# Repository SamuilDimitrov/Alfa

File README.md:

# Alfa

*Alfa представлява модел на ракета която моще да извършва стабилни полети като за стабилизация изполва насочване на вектора на изходните газове на двигателя*

## Как да си сваля и използвам проекта?

За сега не е невъзможно.

## Използвани технологии

* Arduino(https://www.arduino.cc/) - микро контролер
* MPU6050(https://invensense.tdk.com/products/motion-tracking/6-axis/mpu-6050/) - комбиниран акселерометър и жироскоп определящи посоката и ориентацията на ракетата
* BME280(https://www.bosch-sensortec.com/products/environmental-sensors/humidity-sensors-bme280/) - сензор за температура и атмосферно налягане

## Информация за авторите на проекта

* **Самуил Димитров** - *програмист, дизаинер, хардуерист*

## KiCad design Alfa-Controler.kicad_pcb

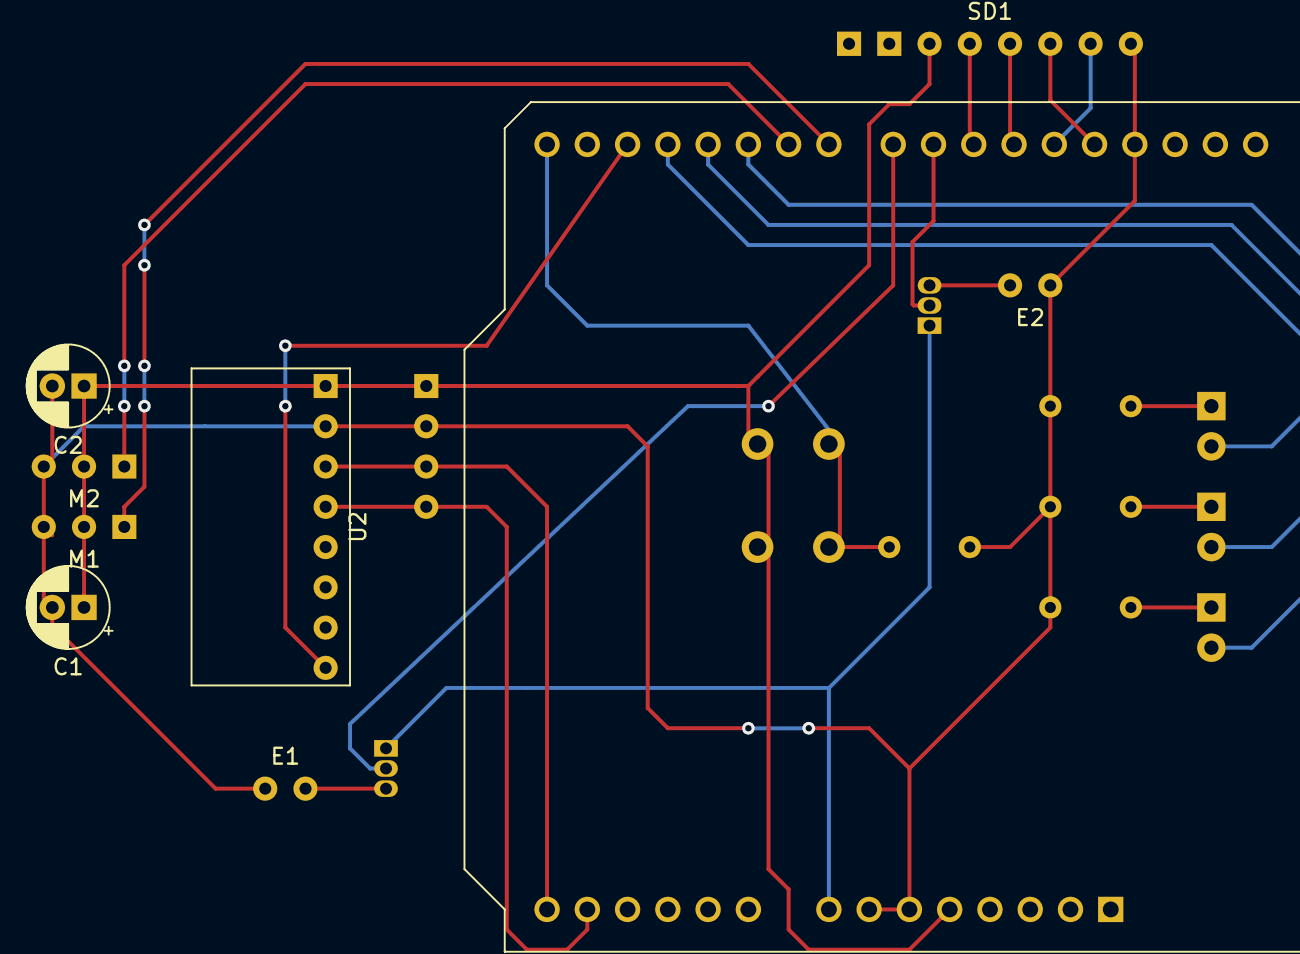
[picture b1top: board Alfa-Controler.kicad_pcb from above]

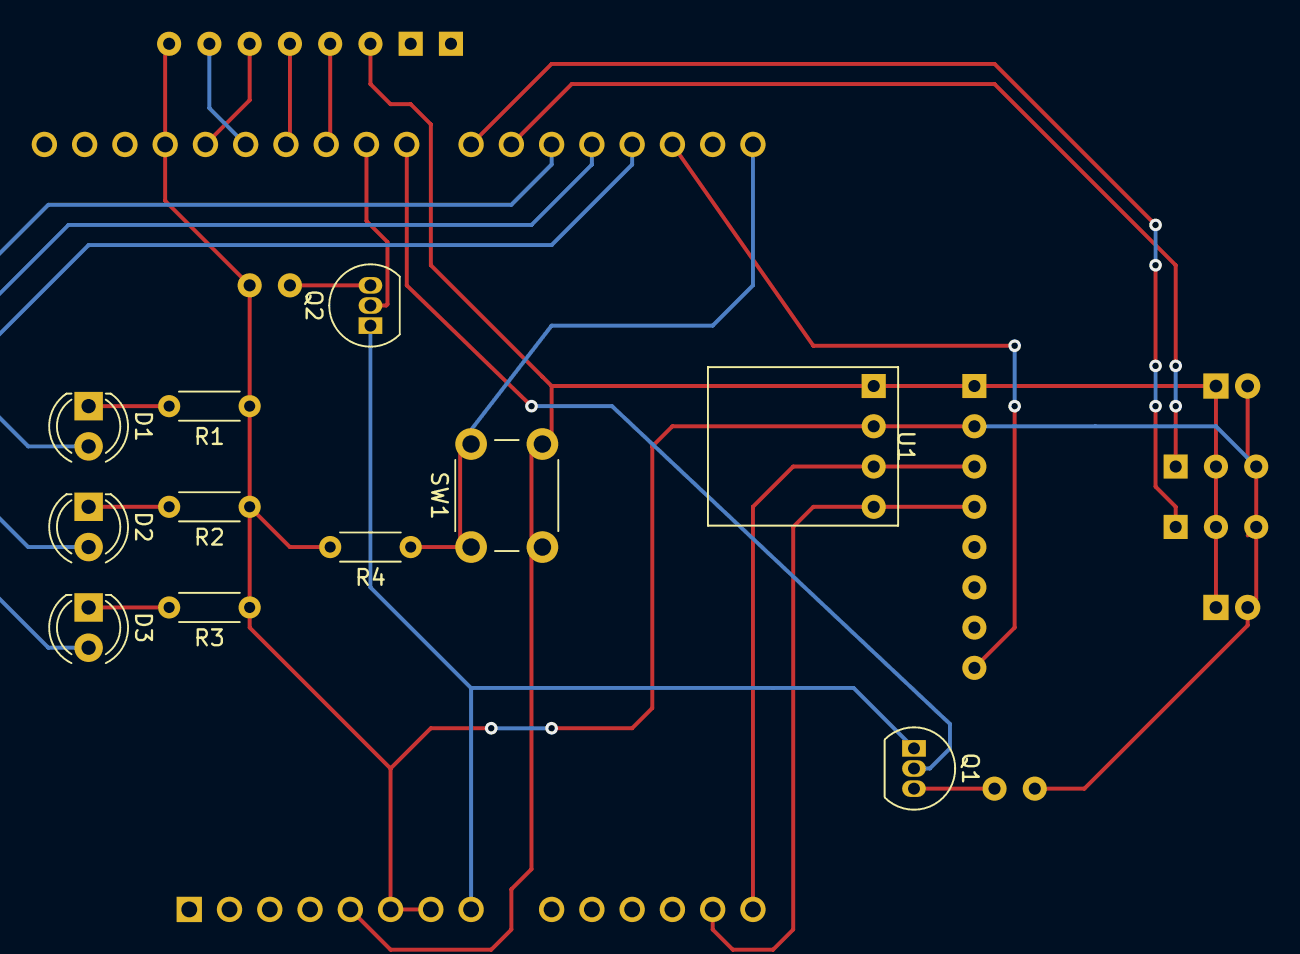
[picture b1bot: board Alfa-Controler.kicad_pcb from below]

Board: 2 copper layers, 20 parts (11 on the bottom side), 23 nets.

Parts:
A1: Arduino_UNO_R3
C1, C2: 100uF; CP_Radial_D5.0mm_P2.00mm
D1: BLUE_LED; LED_D4.0mm
D2: GREEN_LED; LED_D4.0mm
D3: RED_LED; LED_D4.0mm
E1: Ignition_SPARK_GAP; Spark_cable
E2: Piro1_SPARK_GAP; Spark_cable
M1: X-axis Servo; Servo_Pins
M2: Y-axis Servo; Servo_Pins
Q1, Q2: 2N3904; TO-92_Inline
R1, R2, R3: 220; R_Axial_DIN0204_L3.6mm_D1.6mm_P5.08mm_Horizontal
R4: 10k; R_Axial_DIN0204_L3.6mm_D1.6mm_P5.08mm_Horizontal
SD1: SD_CARD
SW1: SW_Push; SW_PUSH_6mm_H4.3mm
U1: BME280_BB; BMP280
U2: MPU-6050BB; MPU6050

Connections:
+5V: A1.5, C1.1, C2.1, M1.2, M2.2, SD1.3, SW1.2, U1.1, U2.1
+9V: A1.8, Q1.1, Q2.1
/D6: A1.21, M2.1
/D7: A1.22, M1.1
/D8: A1.23, Q1.2
/D9: A1.24, Q2.2
/INT: A1.17, U2.8
/SCL_BMP: A1.14, U1.3, U2.3
/SDA_BMP: A1.13, U1.4, U2.4
GND: A1.6, A1.7, A1.29, C1.2, C2.2, E1.1, E2.1, M1.3, M2.3, R1.1, R2.1, R3.1, R4.2, SD1.8, U1.2, U2.2
unnamed: A1.15, R4.1, SW1.1
unnamed: A1.18, D1.2
unnamed: A1.19, D2.2
unnamed: A1.20, D3.2
unnamed: A1.25, SD1.4
unnamed: A1.26, SD1.5
unnamed: A1.27, SD1.7
unnamed: A1.28, SD1.6
unnamed: D1.1, R1.2
unnamed: D2.1, R2.2
unnamed: D3.1, R3.2
unnamed: E1.2, Q1.3
unnamed: E2.2, Q2.3
